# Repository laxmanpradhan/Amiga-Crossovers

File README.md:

# Amiga-Crossovers
KiCAD PCB for Amiga Speaker Kit Crossover Circuit

Speaker Kit can be found here:
https://www.parts-express.com/amiga-mt-tower-speaker-kit-with-knock-down-cabinet--300-7124

Based on the design by Paul Carmody

If you just want to have a set made for yourself, download output\gerber.zip and you can upload this file to any PCB manufacturer to get a quote. Google 'PCB manufacturer' to find options.

If you want to modify the file, download KiCAD and then clone this entire repository.

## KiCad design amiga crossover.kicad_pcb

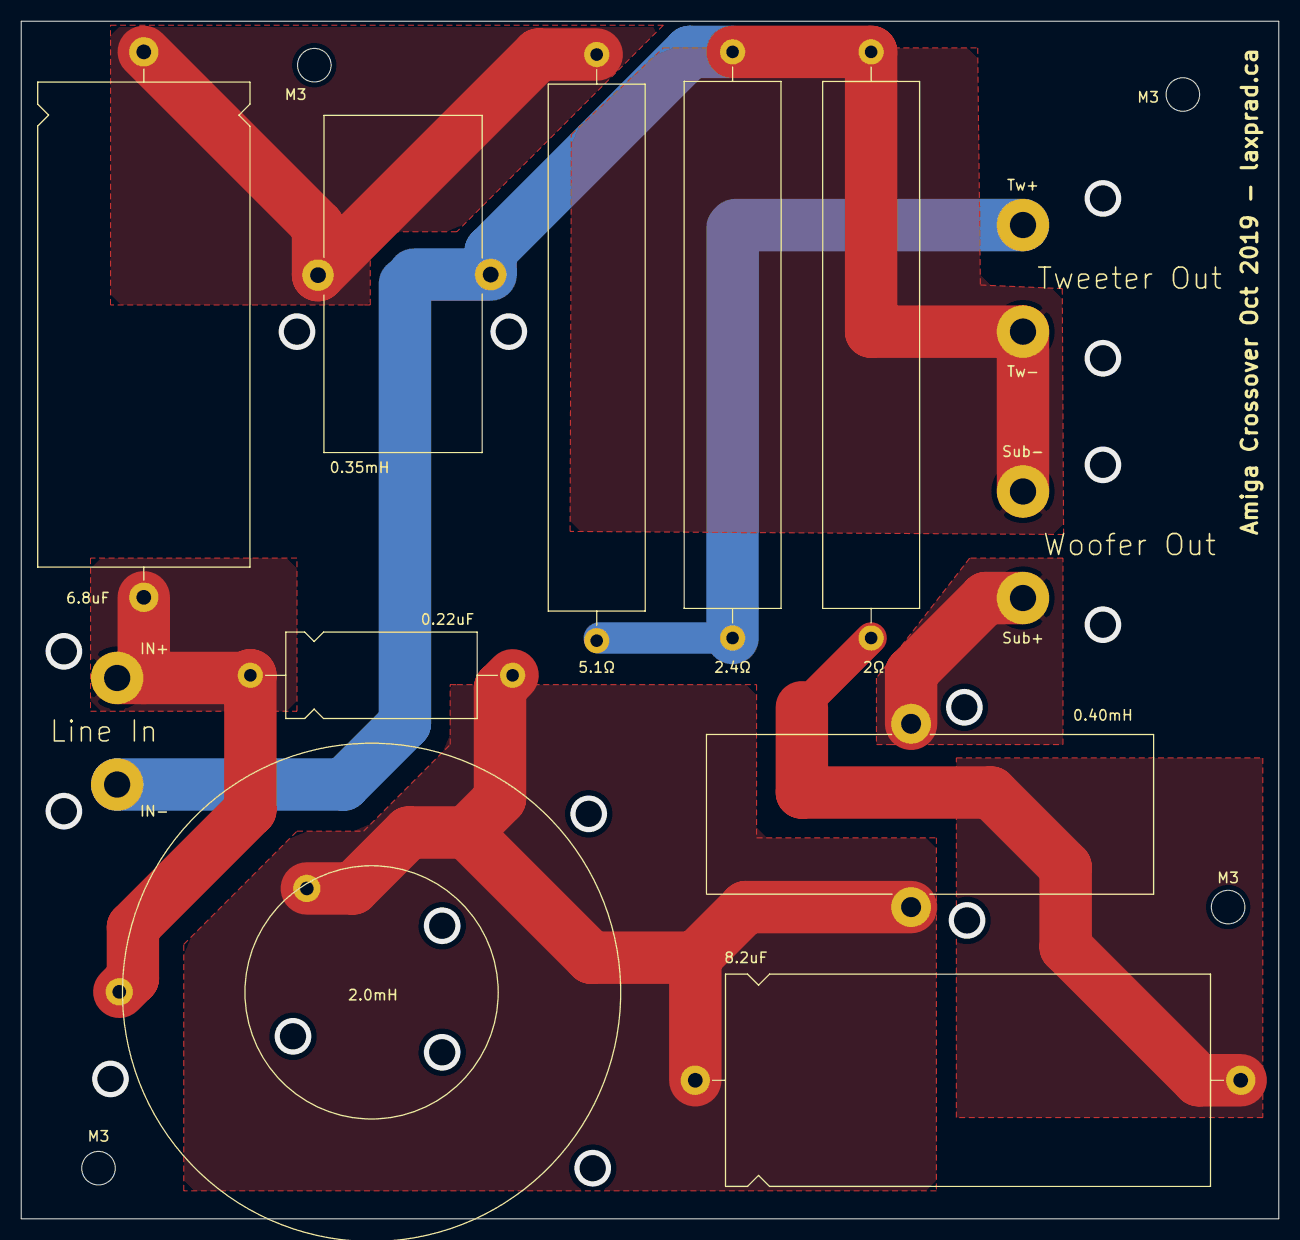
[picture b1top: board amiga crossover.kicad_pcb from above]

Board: 2 copper layers, 119.9 x 114.2 mm, 19 parts (0 on the bottom side), 7 nets.

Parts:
C1: 6.8uF; CP_Axial_L46.0mm_D20.0mm_P52.00mm_Horizontal
C2: 0.22uF; CP_Axial_L18.0mm_D8.0mm_P25.00mm_Horizontal
C3: 8.2uF; CP_Axial_L46.0mm_D20.0mm_P52.00mm_Horizontal
H1: IN+; MountingHole_2.5mm_Pad
H2: IN-; MountingHole_2.5mm_Pad
H3: Tw+; MountingHole_2.5mm_Pad
H4: Tw-; MountingHole_2.5mm_Pad
H5: Sub+; MountingHole_2.5mm_Pad
H6: Sub-; MountingHole_2.5mm_Pad
L1: 0.35mH; L_Toroid_Vertical_L35.1mm_W21.1mm_P18.50mm_Vishay_TJ6
L2: 2.0mH; L_Radial_D40.6mm_P26.16mm_Vishay_IHB-5
L3: 0.40mH; L_Toroid_Vertical_L46.0mm_W19.1mm_P21.80mm_Bourns_5700
M3, M3#2, M3#3, M3#4: MountingHole_3.2mm_M3
R1: 5.1Ω; R_Axial_Power_L50.0mm_W9.0mm_P55.88mm
R2: 2Ω; R_Axial_Power_L50.0mm_W9.0mm_P55.88mm
R3: 2.4Ω; R_Axial_Power_L50.0mm_W9.0mm_P55.88mm

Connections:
unnamed: C1.1, L1.1, R1.2
unnamed: C1.2, C2.1, H1.1, L2.1
unnamed: C2.2, C3.1, L2.2, L3.1
unnamed: C3.2, R2.1
unnamed: H2.1, H4.1, H6.1, L1.2, R2.2, R3.2
unnamed: H3.1, R1.1, R3.1
unnamed: H5.1, L3.2

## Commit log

2019-10-21 updated gerber info

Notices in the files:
amiga crossover.kicad_pcb:
License: Mozilla Public License 2.0
